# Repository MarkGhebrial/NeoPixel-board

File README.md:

# NeoPixel-board

A simple PCB designed in KiCAD to power and control a lage amount of NeoPixels using an Adafruit itsy-bitsy. It can be powered by any suitable 5v power supply.

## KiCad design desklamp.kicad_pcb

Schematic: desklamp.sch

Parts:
C1: 4700uF; CP_Radial_D12.5mm_P5.00mm
J1: Power; TerminalBlock_bornier-2_P5.08mm
J2: Neopixel; TerminalBlock_bornier-3_P5.08mm
J3: POT3; TerminalBlock_bornier-3_P5.08mm
JP1: Pot3 Jumper; SolderJumper-3_P1.3mm_Bridged12_Pad1.0x1.5mm_NumberLabels
MH0, MH1, MH2, MH3: MountingHole; MountingHole_3.2mm_M3
R1: 470ohm; R_Axial_DIN0207_L6.3mm_D2.5mm_P10.16mm_Horizontal
RV0: POT0; TerminalBlock_bornier-3_P5.08mm
RV1: POT1; TerminalBlock_bornier-3_P5.08mm
RV2: POT2; TerminalBlock_bornier-3_P5.08mm
U1: itsy_bitsy

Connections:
+5V: C1.1, J1.2, J2.3, J3.2, RV0.2, RV1.2, RV2.2, U1.2 (5V)
GND: C1.2, J1.1, J2.1, J3.3, RV0.1, RV1.1, RV2.1, U1.4 (GND)
unnamed: J2.2, R1.1
unnamed: J3.1, JP1.2
unnamed: JP1.1, U1.8 (A3)
unnamed: JP1.3, U1.26 (9`)
unnamed: RV0.3, U1.5 (A0)
unnamed: RV1.3, U1.6 (A1)
unnamed: RV2.3, U1.7 (A2)
Signal: R1.2, U1.24 (5`)

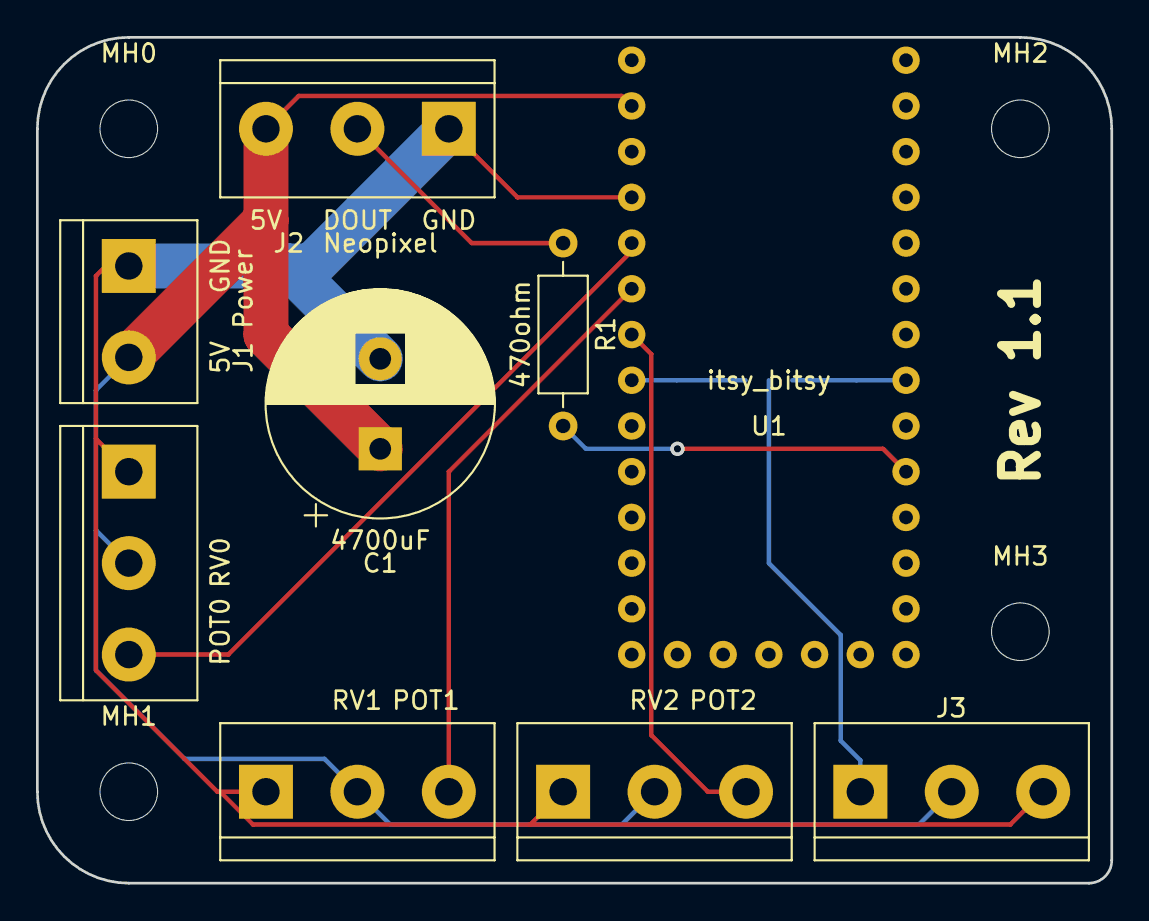
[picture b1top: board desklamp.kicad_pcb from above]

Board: 2 copper layers, 59.7 x 47.0 mm, 14 parts (1 on the bottom side), 10 nets.

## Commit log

2021-02-19 Ditch the ATtiny, go with itsy-bitsy
2021-02-19 Work on pcb and generate gerbers
2021-02-19 Total PCB redesign
2021-02-19 Adjusted PCB and routed traces
2021-02-20 Moved some traces to front and added revision number
    Rev 1.0
2021-02-22 Added a jumper for POT3 so that it can be used as a second NeoPixel port
2021-02-23 Move JP1
